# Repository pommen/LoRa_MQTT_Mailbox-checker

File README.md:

# LoRa_MQTT_Mailbox-checker
My version of a mailbox check using LoRa RFM95 module on a custom arduino pro mini with 18650battery. communicating with a ESP8266 

ISP pins on the board mounted on the mailbox is mirrored. If used, either burn boot loader before mounting the 328p. Or use dupoint wires to connect to the programmer.

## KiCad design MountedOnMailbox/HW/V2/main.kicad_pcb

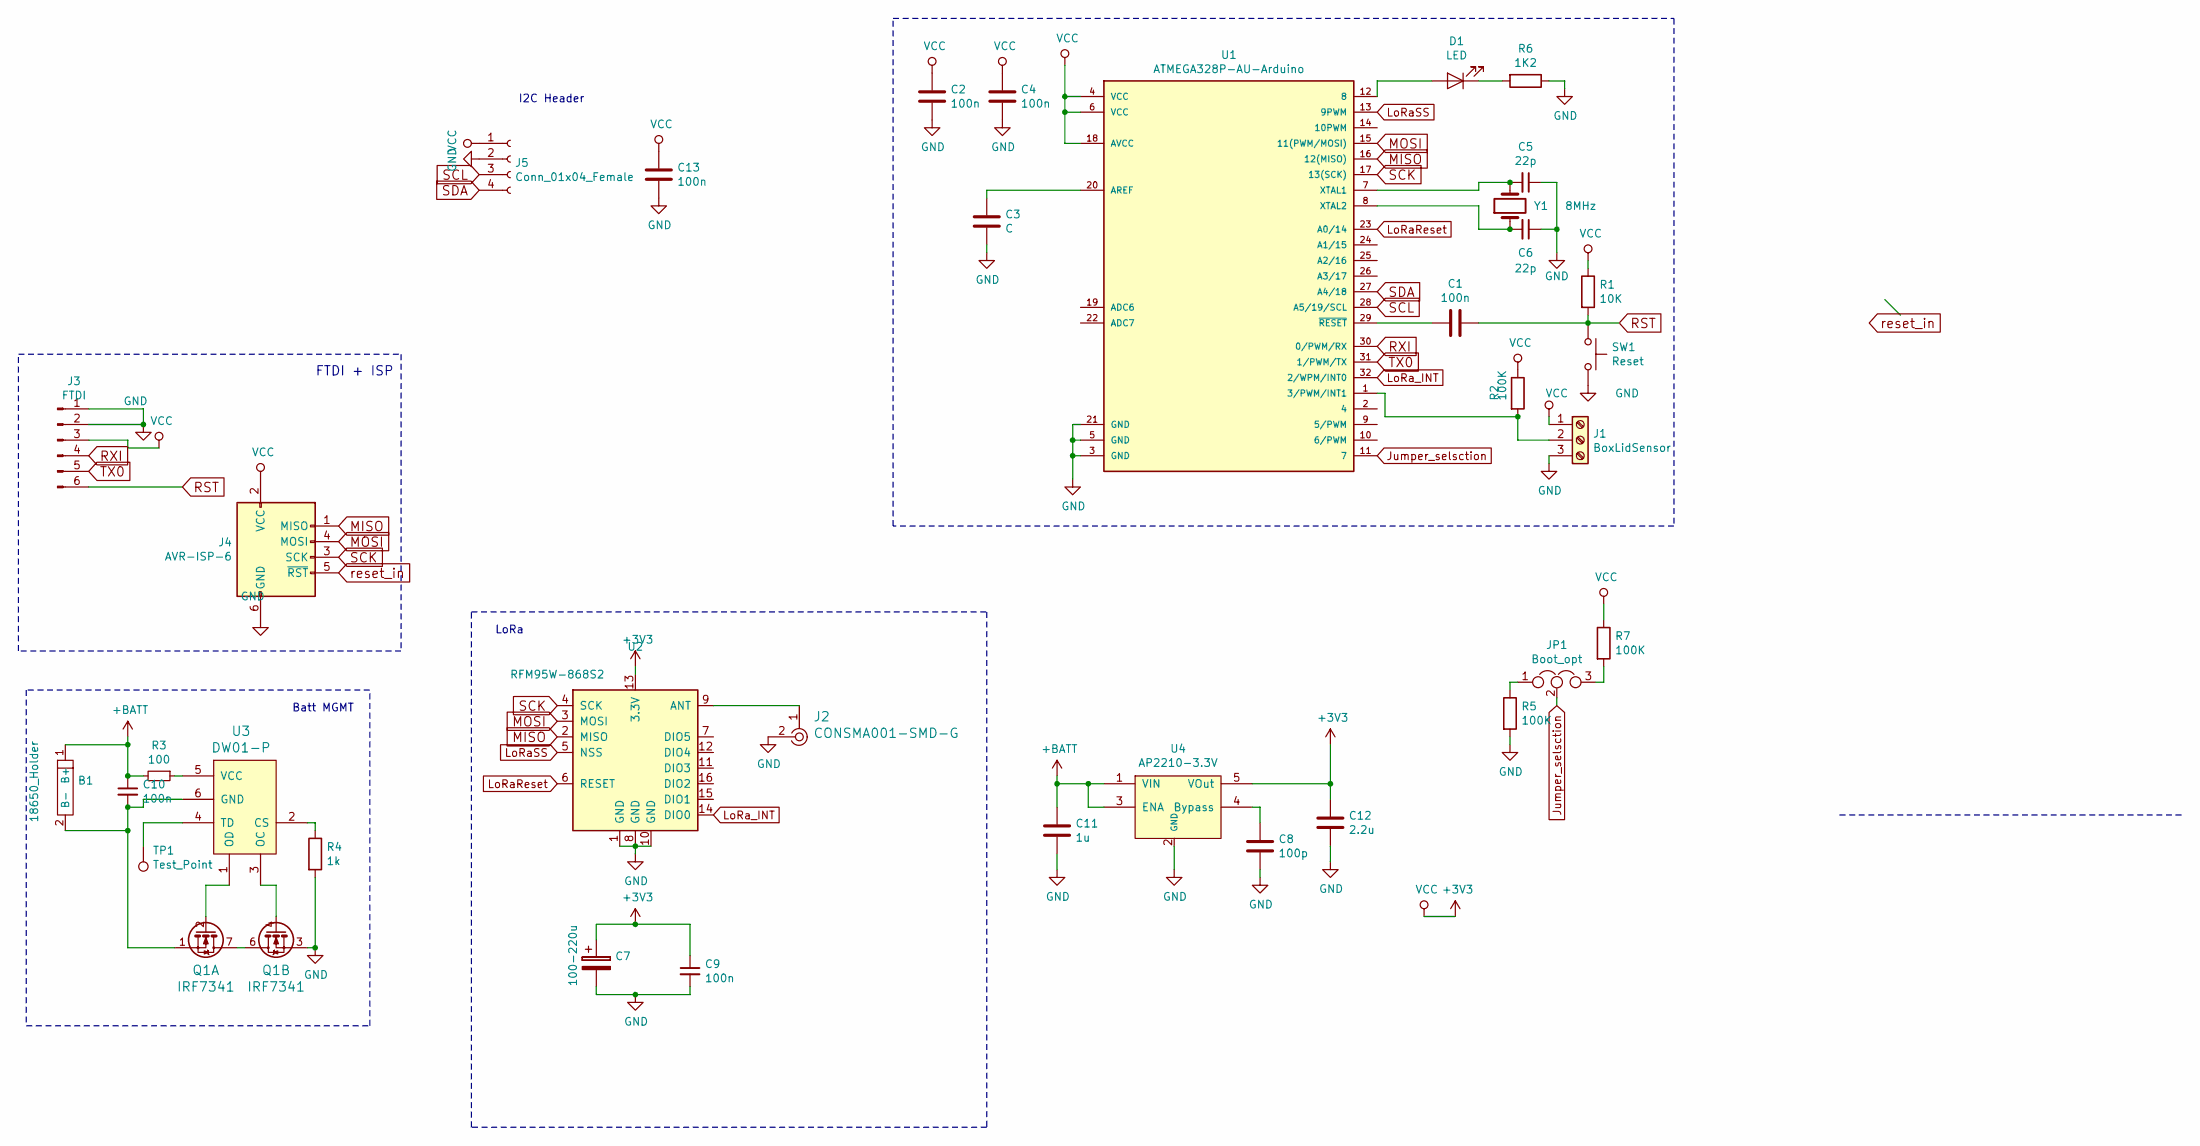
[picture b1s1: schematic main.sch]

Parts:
B1: 18650_Holder; 18650-PC2_holder
C1, C2, C4, C9, C10, C13: 100n; C_0805_2012Metric_Pad1.15x1.40mm_HandSolder
C3: C; C_0805_2012Metric_Pad1.15x1.40mm_HandSolder
C5, C6: 22p; C_0805_2012Metric_Pad1.15x1.40mm_HandSolder
C7: 100-220u; D_SMB
C8: 100p; C_0805_2012Metric_Pad1.15x1.40mm_HandSolder
C11: 1u; C_0805_2012Metric_Pad1.15x1.40mm_HandSolder
C12: 2.2u; C_0805_2012Metric_Pad1.15x1.40mm_HandSolder
D1: LED; LED_0805_2012Metric_Pad1.15x1.40mm_HandSolder
J1: BoxLidSensor; TerminalBlock_Phoenix_PT-1,5-3-3.5-H_1x03_P3.50mm_Horizontal
J2: CONSMA001-SMD-G; SMA_edge connector; MPN CONSMA001-SMD-G; Digi-Key_PN CONSMA001-SMD-G-ND
J3: FTDI; PinSocket_1x06_P2.54mm_Vertical
J4: AVR-ISP-6; PinSocket_2x03_P2.54mm_Vertical
J5: Conn_01x04_Female; PinHeader_1x04_P2.54mm_Vertical
JP1: Boot_opt; SolderJumper-3_P1.3mm_Open_RoundedPad1.0x1.5mm
Q1: IRF7341; SOIC-8_3.9x4.9mm_P1.27mm
R1: 10K; R_0805_2012Metric_Pad1.15x1.40mm_HandSolder
R2, R5, R7: 100K; R_0805_2012Metric_Pad1.15x1.40mm_HandSolder
R3: 100; R_0805_2012Metric_Pad1.15x1.40mm_HandSolder
R4: 1k; R_0805_2012Metric_Pad1.15x1.40mm_HandSolder
R6: 1K2; R_0805_2012Metric_Pad1.15x1.40mm_HandSolder
SW1: Reset; PushBTN KSC241G
TP1: Test_Point; TestPoint_Pad_D1.0mm
U1: ATMEGA328P-AU-Arduino; TQFP-32_7x7mm_P0.8mm
U2: RFM95W-868S2; HOPERF_RFM9XW_SMD
U3: DW01-P; TSOT-23-6_HandSoldering
U4: AP2210-3.3V; SOT-23-5_HandSoldering
Y1: 8MHz; Crystal_SMD_ECS_CSM3X-2Pin_7.6x4.1mm

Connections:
+3V3: C2.1, C4.1, C7.1, C9.1, C12.1, C13.1, J1.1, J3.3, J4.2 (VCC), J5.1, R1.1, R2.1, R7.1, U1.4 (VCC), U1.6 (VCC), U1.18 (AVCC), U2.13 (3.3V), U4.5 (VOut)
+BATT: B1.1 (B+), C10.1, C11.1, R3.2, U4.1 (VIN), U4.3 (ENA)
GND: C2.2, C3.2, C4.2, C5.1, C6.1, C7.2, C8.2, C9.2, C11.2, C12.2, C13.2, J1.3, J2.2, J3.1, J3.2, J4.6 (GND), J5.2, Q1.3, R4.2, R5.2, R6.1, SW1.2, U1.3 (GND), U1.5 (GND), U1.21 (GND), U2.1 (GND), U2.8 (GND), U2.10 (GND), U4.2 (GND)
Jumper_selsction: JP1.2, U1.11 (7)
LoRaReset: U1.23 (A0/14), U2.6 (RESET)
LoRaSS: U1.13 (9PWM), U2.5 (NSS)
LoRa_INT: U1.32 (2/WPM/INT0), U2.14 (DIO0)
MISO: J4.1 (MISO), U1.16 (12(MISO)), U2.2 (MISO)
MOSI: J4.4 (MOSI), U1.15 (11(PWM/MOSI)), U2.3 (MOSI)
unnamed: B1.2 (B-), C10.2, Q1.1, U3.6 (GND)
unnamed: C1.2, U1.29 (~RESET~)
unnamed: C3.1, U1.20 (AREF)
unnamed: C5.2, U1.7 (XTAL1), Y1.2
unnamed: C6.2, U1.8 (XTAL2), Y1.1
unnamed: C8.1, U4.4 (Bypass)
unnamed: D1.1 (K), R6.2
unnamed: D1.2 (A), U1.12 (8)
unnamed: J1.2, R2.2, U1.1 (3/PWM/INT1)
unnamed: J2.1, U2.9 (ANT)
unnamed: JP1.1, R5.1
unnamed: JP1.3, R7.2
unnamed: Q1.2, U3.1 (OD)
unnamed: Q1.4, U3.3 (OC)
unnamed: Q1.5, Q1.6, Q1.7, Q1.8
unnamed: R3.1, U3.5 (VCC)
unnamed: R4.1, U3.2 (CS)
unnamed: TP1.1, U3.4 (TD)
RST: C1.1, J3.6, R1.2, SW1.1
RXI: J3.4, U1.30 (0/PWM/RX)
SCK: J4.3 (SCK), U1.17 (13(SCK)), U2.4 (SCK)
SCL: J5.3, U1.28 (A5/19/SCL)
SDA: J5.4, U1.27 (A4/18)
TX0: J3.5, U1.31 (1/PWM/TX)
reset_in: J4.5 (~RST)

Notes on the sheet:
FTDI + ISP
Batt MGMT
LoRa
I2C Header

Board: 2 copper layers, 36 parts (1 on the bottom side), 33 nets, no tracks yet.

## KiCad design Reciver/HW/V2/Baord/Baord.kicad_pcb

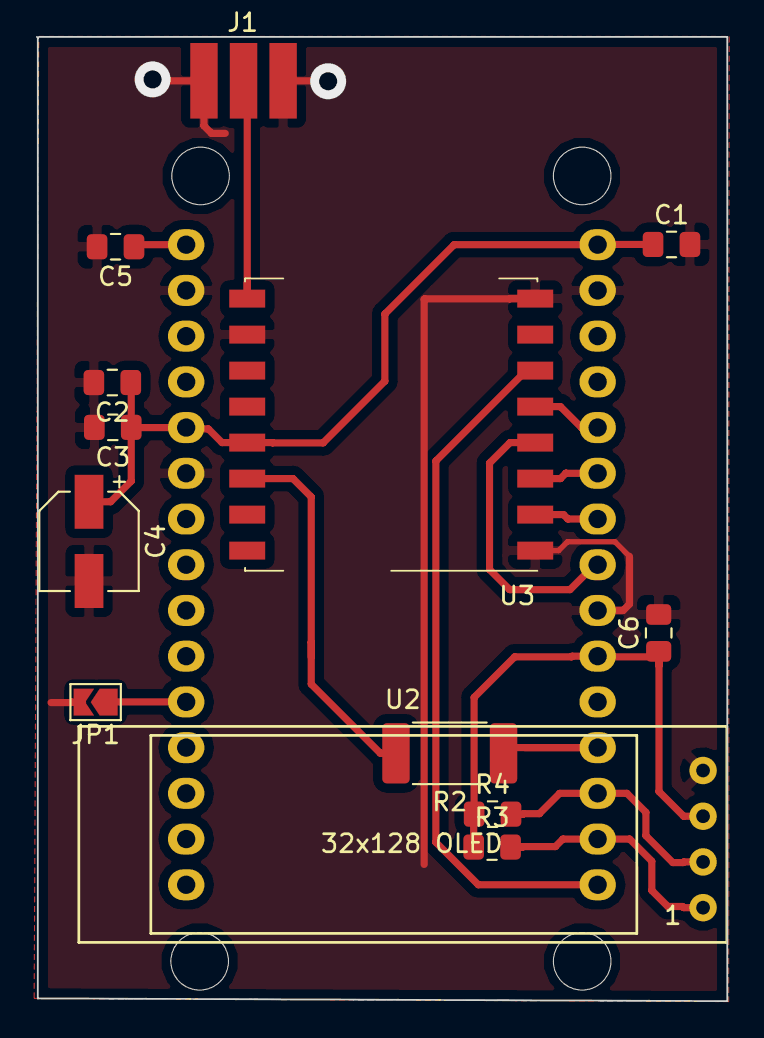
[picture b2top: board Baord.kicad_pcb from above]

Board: 2 copper layers, 38.4 x 53.6 mm, 14 parts (1 on the bottom side), 14 nets.

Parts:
C1, C2, C5, C6: 100n; C_0805_2012Metric_Pad1.15x1.40mm_HandSolder
C3: C; C_0805_2012Metric_Pad1.15x1.40mm_HandSolder
C4: CP; CP_Elec_5x5.9
J1: Edge_Connector; SMA_edge connector
JP1: Jumper; SolderJumper-2_P1.3mm_Open_TrianglePad1.0x1.5mm
R2: 0R; R_2512_6332Metric_Pad1.52x3.35mm_HandSolder
R3, R4: 10K; R_0805_2012Metric_Pad1.15x1.40mm_HandSolder
U1: NodeMCU_1.0_(ESP-12E); NodeMCU_Amica_R2
U2: OLED_128x32_i2c; OLED_128x32_I2C
U3: RFM95W-868S2; HOPERF_RFM9XW_SMD

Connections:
CS: U1.20, U3.5
GND: C1.2, C2.2, C3.2, C4.2, C5.2, C6.2, J1.2, JP1.2, U1.10, U1.14, U1.17, U1.24, U2.4, U3.1, U3.8, U3.10
I2C_SCL: R4.2, U1.28, U2.2
I2C_SDA: R3.2, U1.29, U2.1
INT: R2.1, U1.27
MISO: U1.22, U3.2
MOSI: U1.21, U3.3
unnamed: C5.1, U1.15
unnamed: J1.1, U3.9
unnamed: JP1.1, U1.5
unnamed: R2.2, U3.14
RESET: U1.30, U3.6
SCK: U1.23, U3.4
VCC: C1.1, C2.1, C3.1, C4.1, C6.1, R3.1, R4.1, U1.11, U1.16, U1.25, U2.3, U3.13

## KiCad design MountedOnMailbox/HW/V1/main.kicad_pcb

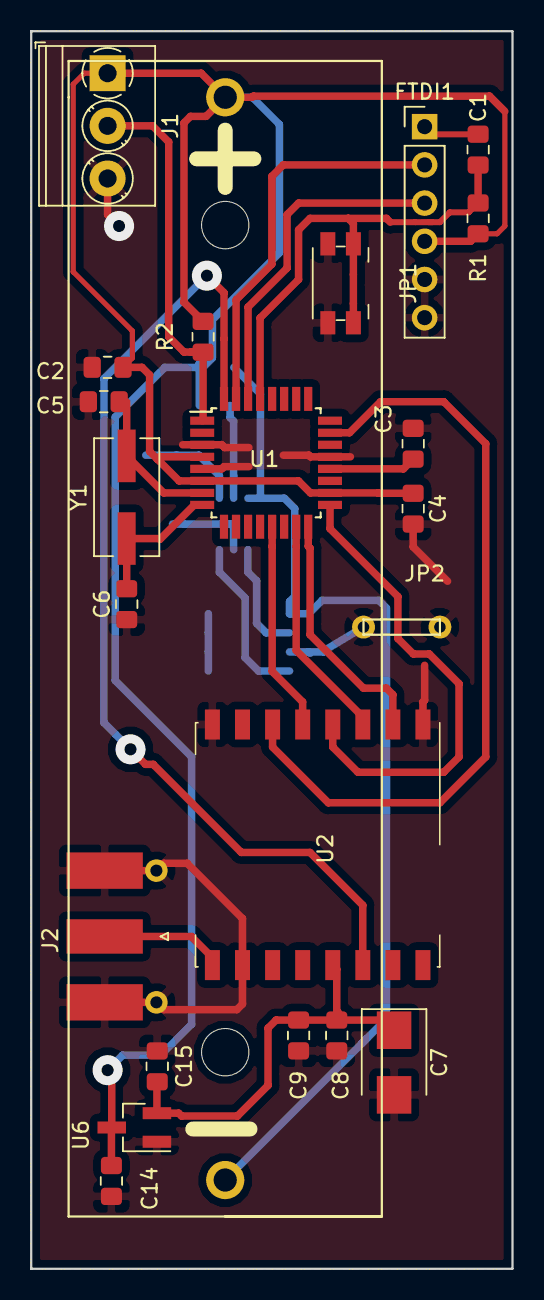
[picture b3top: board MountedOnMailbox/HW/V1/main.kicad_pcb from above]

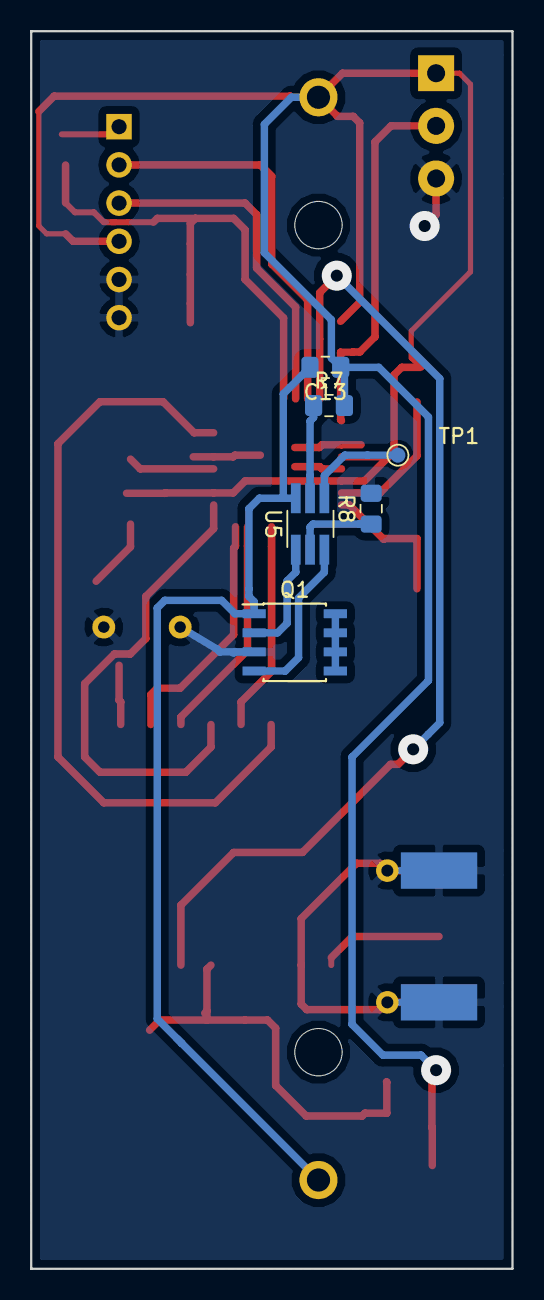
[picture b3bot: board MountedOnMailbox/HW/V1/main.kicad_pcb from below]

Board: 2 copper layers, 32.0 x 82.3 mm, 29 parts (6 on the bottom side), 25 nets.

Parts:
B1: 18650_Holder; 18650-PC2_holder
C1, C2, C3, C4: C; C_0805_2012Metric_Pad1.15x1.40mm_HandSolder
C5, C6: 22p; C_0805_2012Metric_Pad1.15x1.40mm_HandSolder
C7: 100-220u; D_SMB
C8: 10u; C_0805_2012Metric_Pad1.15x1.40mm_HandSolder
C9, C13: 100n; C_0805_2012Metric_Pad1.15x1.40mm_HandSolder
C14, C15: 1u; C_0805_2012Metric_Pad1.15x1.40mm_HandSolder
FTDI1: FTDI; PinHeader_1x06_P2.54mm_Vertical
J1: BoxLidSensor; TerminalBlock_Phoenix_PT-1,5-3-3.5-H_1x03_P3.50mm_Horizontal
J2: CONSMA001-SMD-G; SMA_Molex_73251-1153_EdgeMount_Horizontal
JP1: Jumper; Panasonic_EVQPUJ_EVQPUA
JP2: Jumper; JUMPER_5MM
Q1: IRF7341; SOIC-8_3.9x4.9mm_P1.27mm
R1: 10K; R_0805_2012Metric_Pad1.15x1.40mm_HandSolder
R2: 100K; R_0805_2012Metric_Pad1.15x1.40mm_HandSolder
R7: 100; R_0805_2012Metric_Pad1.15x1.40mm_HandSolder
R8: 1k; R_0805_2012Metric_Pad1.15x1.40mm_HandSolder
TP1: Test_Point; TestPoint_Pad_D1.0mm
U1: ATMEGA328P; TQFP-32_7x7mm_P0.8mm
U2: RFM95W-868S2; HOPERF_RFM9XW_SMD
U5: DW01-P; TSOT-23-6_HandSoldering
U6: XC6206P332MR; SOT-23_Handsoldering
Y1: 8MHz; Crystal_SMD_ECS_CSM3X-2Pin_7.6x4.1mm

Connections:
+3V3: C7.1, C8.1, C9.1, C15.1, U2.13, U6.2
+BATT: B1.1, C2.1, C4.1, C13.1, C14.1, FTDI1.4, J1.1, R1.1, R2.1, R7.2, U1.4, U1.6, U1.18, U6.3
GND: C2.2, C3.2, C4.2, C5.1, C6.1, C7.2, C8.2, C9.2, C14.2, C15.2, FTDI1.5, FTDI1.6, J1.3, J2.2, JP1.2, JP2.1, JP2.2, Q1.3, R8.2, U1.3, U1.5, U1.21, U2.1, U2.8, U2.10, U6.1
LoRaReset: U1.23, U2.6
LoRaSS: U1.13, U2.5
LoRa_INT: U1.32, U2.14
MISO: U1.16, U2.2
MOSI: U1.15, U2.3
unnamed: B1.2, C13.2, Q1.1, U5.6
unnamed: C3.1, U1.20
unnamed: C5.2, U1.7, Y1.2
unnamed: C6.2, U1.8, Y1.1
unnamed: J1.2, R2.2, U1.1
unnamed: J2.1, U2.9
unnamed: Q1.2, U5.1
unnamed: Q1.4, U5.3
unnamed: Q1.5, Q1.6, Q1.7, Q1.8
unnamed: R7.1, U5.5
unnamed: R8.1, U5.2
unnamed: TP1.1, U5.4
RST: C1.1, FTDI1.1
RXI: FTDI1.3, U1.30
SCK: U1.17, U2.4
TX0: FTDI1.2, U1.31
reset_in: C1.2, JP1.1, R1.2, U1.29

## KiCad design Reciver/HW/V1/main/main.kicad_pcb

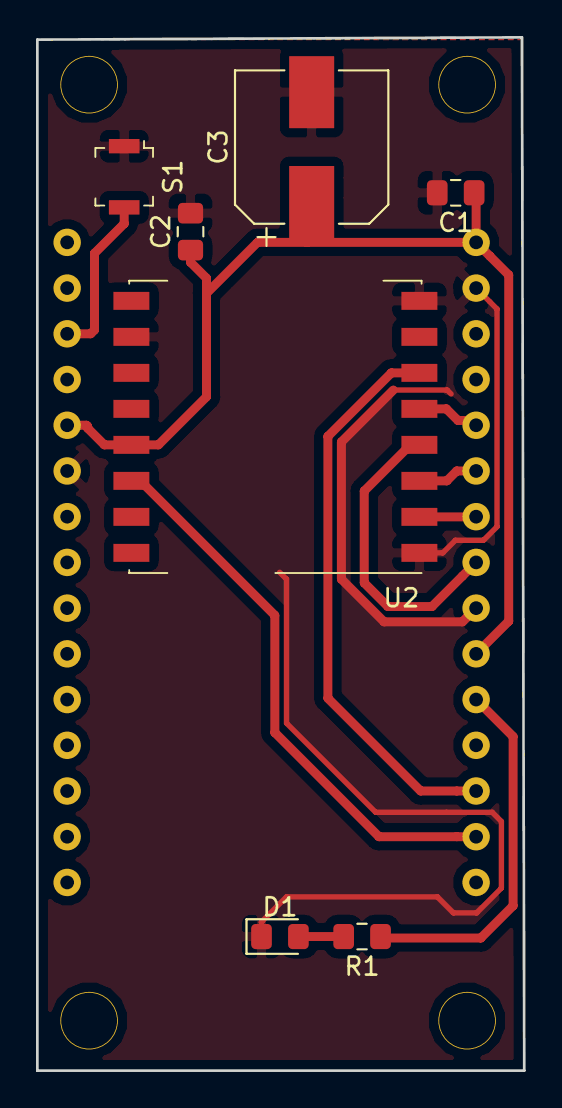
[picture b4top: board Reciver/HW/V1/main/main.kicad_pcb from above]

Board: 2 copper layers, 27.1 x 57.4 mm, 8 parts (1 on the bottom side), 11 nets.

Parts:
C1, C2: C; C_0805_2012Metric_Pad1.15x1.40mm_HandSolder
C3: CP; CP_Elec_8x6.7
D1: LED; LED_0805_2012Metric_Pad1.15x1.40mm_HandSolder
R1: 1K; R_0805_2012Metric_Pad1.15x1.40mm_HandSolder
S1: GPTS203211B; Switch_Tactile_SMD_B3U-1000P
U1: NodeMCU_1.0_(ESP-12E); NodeMCU-LoLinV3
U2: RFM95W-868S2; HOPERF_RFM9XW_SMD

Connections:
CS: U1.20, U2.5
GND: C1.2, C2.2, C3.2, D1.1, S1.1, U1.10, U1.14, U1.17, U1.24, U2.1, U2.8, U2.10
INT: U1.29, U2.14
MISO: U1.22, U2.2
MOSI: U1.21, U2.3
unnamed: D1.2, R1.2
unnamed: R1.1, U1.26
unnamed: S1.2, U1.13
RESET: U1.28, U2.6
SCK: U1.23, U2.4
VCC: C1.1, C2.1, C3.1, U1.11, U1.16, U1.25, U2.13

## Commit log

2018-08-04 The sender module, first upload
2018-08-04 first commit of the reciver end
2018-08-05 Done
2018-08-05 delteted my password
2018-08-05 revicer, bad NODEMCU footprint
2018-08-05 Better foorprint
2018-08-12 layout
    kicad
2018-09-06 iBOM
2018-09-14 ICP header warning
2018-09-23 adsd
2018-09-23 cleanup
2018-10-18 Better layout
    And i2c header
2018-11-15 cencored my L/P
